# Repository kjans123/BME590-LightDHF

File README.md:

# BME590-LightDHF
Design History Files & project plan for BME 590 LED light design challenge
test

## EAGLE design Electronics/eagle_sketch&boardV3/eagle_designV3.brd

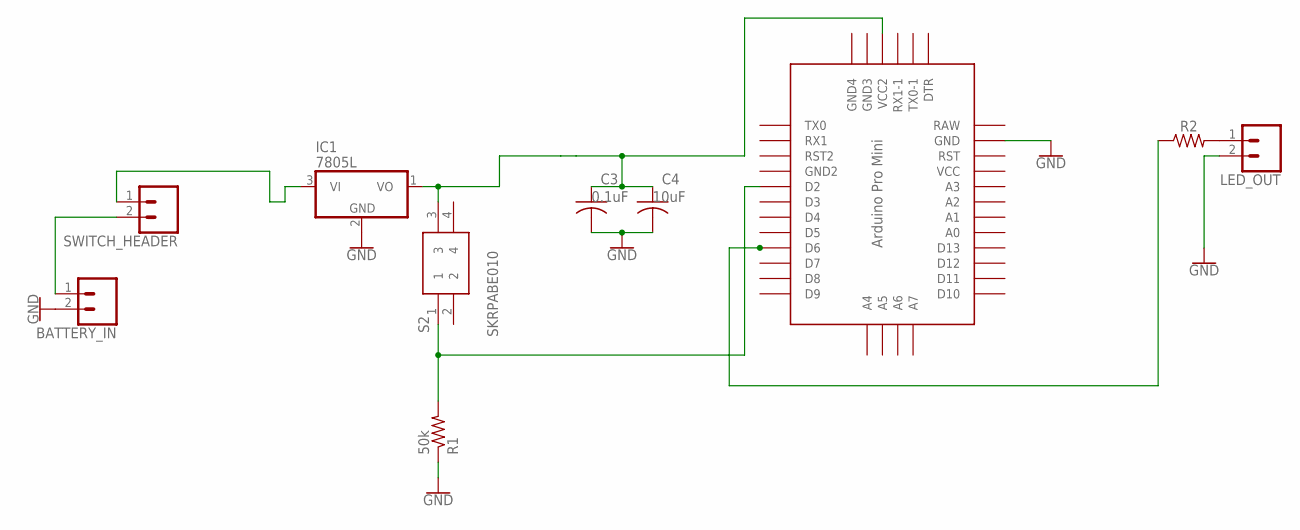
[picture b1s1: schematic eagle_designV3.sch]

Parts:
BATTERY_IN: CONN_02; 1X02
C3: 0.1uF; C0805
C4: 10uF; C0805
IC1: 7805L; TO92
LED_OUT: CONN_02; 1X02
R1: 50k; R0805
R2: 330; R0805
S2: SKRPABE010; SMT(4.2X3.2)
SWITCH_HEADER: CONN_02; 1X02
U$1: PRO-MINI

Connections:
GND: BATTERY_IN.2, C3.2, C4.2, IC1.2 (GND), LED_OUT.2, R1.1, U$1.GND
unnamed: BATTERY_IN.1, SWITCH_HEADER.2
unnamed: IC1.3 (VI), SWITCH_HEADER.1
unnamed: C3.1, C4.1, IC1.1 (VO), S2.3, U$1.VCC1 (VCC2)
unnamed: R1.2, S2.1, U$1.D2
unnamed: R2.1, U$1.D6
unnamed: LED_OUT.1, R2.2
RAW: U$1.RAW

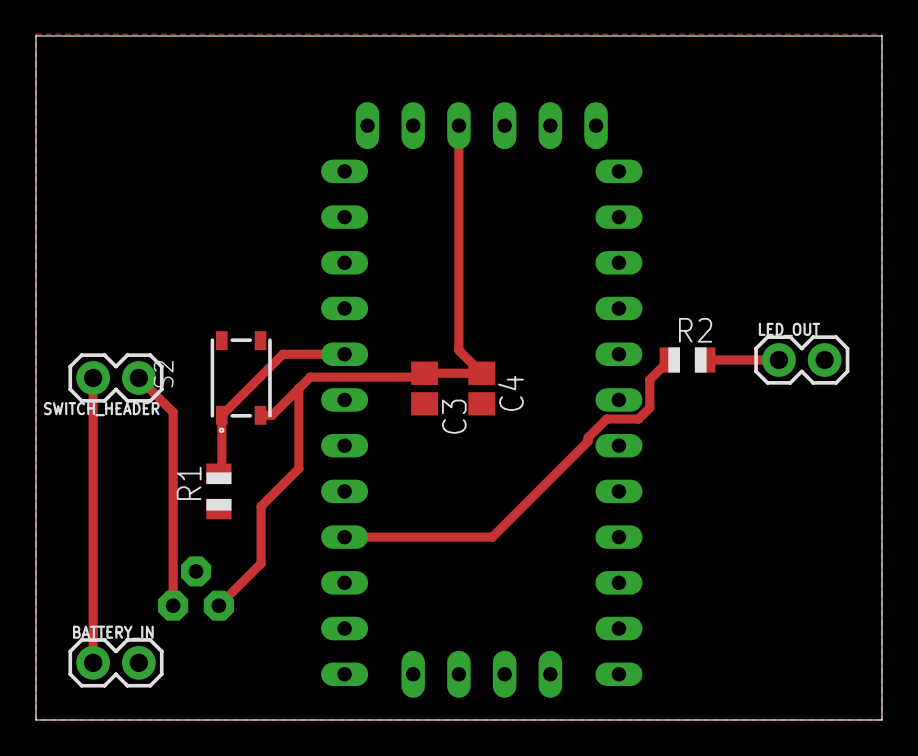
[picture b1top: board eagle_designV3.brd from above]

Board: 2 copper layers, 47.0 x 38.0 mm, 10 parts (1 on the bottom side), 7 nets.

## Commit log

2018-09-28 initial commit for Milestone1 assignment
2018-09-28 added timer chip to electronics BOM txt file (close #1)
2018-09-28 decided to use analog design for LED light (close #2)
2018-09-30 readme change
2018-09-30 changed readme
2018-09-30 ssh key troubleshooting
2018-10-05 added initial concepts and filtering workbook (closes #5)
2018-10-19 removed timer chip entry to reflect change from analog solution to MCU solution (close #3)
2018-10-19 researched different MCU's. Decided on Arduino Pro Mini (close #8)
2018-10-20 changed pro mini link and price
2018-10-24 added concepts and filtering for shock absorption (close #17)
2018-10-24 moved Shock xlsx file to Mechanical folder
2018-10-25 model V1 of bulb holder. Based design on grommet 9600K115 from McMaster Carr
2018-10-25 updated MechNotes to include bulb holder and grommet for bulb_grommet_holderV1
2018-10-25 Update MechNotes with date
2018-10-25 Print update
2018-10-25 added basic Functional Block diagram (close #4)
2018-10-25 Update ElecNotes to reflect MCU design choice
2018-10-26 version 1 of circuit diagram(closes #18)
2018-10-26 added version 1 of very rough sketch of physical enclosure (closes #6)
2018-10-29 initial code for Switching LED outputs
2018-10-29 built bare minimum breadboard circuit with LED and basic pushbutton (closes #13)
2018-10-29 V1 software flowchart for MCU (closes #21)
2018-10-29 changed V1 holder after testing physical grommet so that dimensions are larger (changed outer hole dimension and lip-hole dimension)
2018-10-29 Update for V2 changes for bulb_grommet_holder
2018-10-31 updated circuit diagram to add Zener diode, master switch and parallel bypass caps
2018-10-31 added Archive folder for old docs
2018-10-31 version 2 code for SwitchOutputsCode_V1.ino
2018-11-02 wrote working code to get light to switch brigtnesses & flash (close #12)
2018-11-03 first pass at creating a VERY rough circuit schematic in Eagle
2018-11-03 image of v1 eagle schematic
2018-11-08 built board and refined schematic for V2 circuit (closes#10, closes #24)
2018-11-14 updated board and schematic with post review suggestions from Issue 30
2018-11-17 updated board to reflect toggle switch change
2018-11-18 first REAL versions of every part for enclosure
2018-11-29 updated board and schematic to reflect removal of resistor btwn battery and voltage reg
2018-11-29 changed software to reflect change of PIN-OUT to pin 6 on Pro Mini
2018-11-29 changed bottom piece, pull bar piece and grommet_holder to updateneeded changes after initial prints
2018-11-29 test key
2018-11-29 changed bulb_grommet holder to have wider pin holes and smaller overall diameter
2018-12-06 ensuring all mech files are updated

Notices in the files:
parts and their libraries:
SparkFun-Connectors: Licensing: Creative Commons ShareAlike 4.0 International - https://creativecommons.org/licenses/by-sa/4.0
